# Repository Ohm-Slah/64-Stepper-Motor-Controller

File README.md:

# 64-Stepper-Motor-Controller
Controls an 8x8 array of stepper motors and RGB LED light strips, intended for audio/visual performance of a MIDI-like structure. You can certainly make this project with an FPGA, but I don't have much knowledge of FPGA's, so this project is written in C/C++ with the Arduino library included. Due to the incredible number of I/O, three Teensy microcontrollers are currently implemented, two Teensy 4.0's for I/O drivers (32 motors each), and one Teensy 4.1 for the 'main brain'. 

# Concetual initial design
General layout thoughts for such a large number of stepper motors and how to control them. Revision A is mostly based off of Concept #3.

# Revision A
This design is an attempt to create a fairly modular assembly for 64 stepper motor control. Each A4988 stepper driver can be extracted or replaced if neccessary. Eight total A4988 stepper drivers can be placed onto a single driver 'card'. These are designed to be edge-card connected to a larger board, the 32-stepper board. This board holds four driver cards, totalling to 32 stepper motors. There are 2 of these boards to total 64 motor drivers, with each having 20 74HC595 shift registers for I/O management, and visual indicator LED's for all outputs of the shift registers. Power is supplied to this board via a high-current connector. Both of these 32-stepper boards are then connected to a 'main board' containing the 3 microcontrollers, LED strip connections, and USB connection. 

## 8 Stepper PCB Card

## 32 Stepper PCB Board

## 64 Stepper PCB Board

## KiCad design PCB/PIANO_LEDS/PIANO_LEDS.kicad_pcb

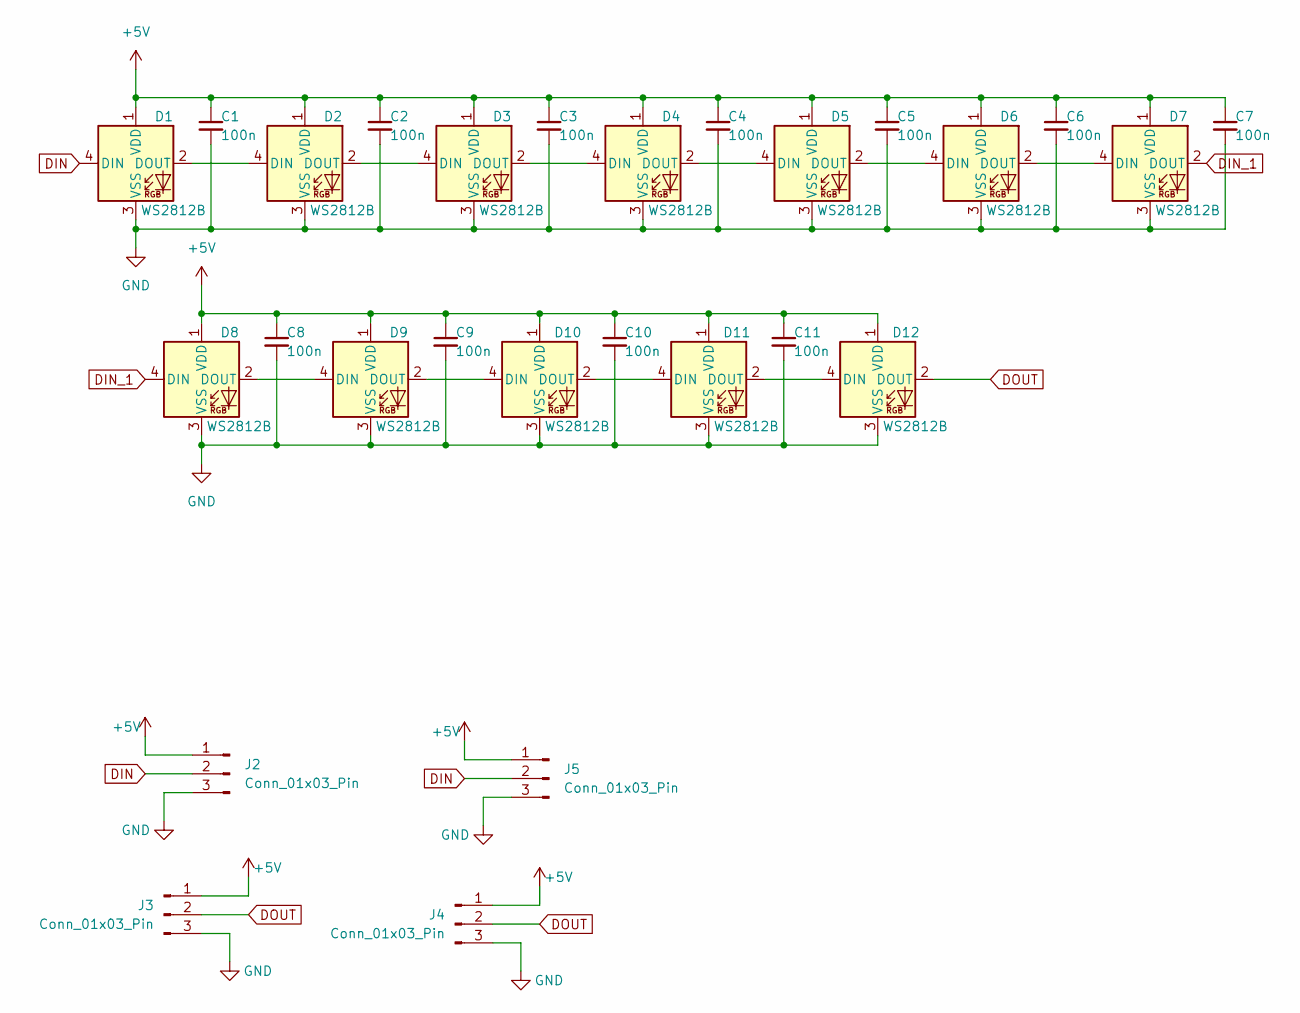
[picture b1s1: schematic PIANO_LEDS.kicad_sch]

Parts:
C1, C2, C3, C4, C5, C6, C7, C8, C9, C10, C11: 100n; C_0603_1608Metric
D1, D2, D3, D4, D5, D6, D7, D8, D9, D10, D11, D12: WS2812B; LED_WS2812B_PLCC4_5.0x5.0mm_P3.2mm
J2, J3, J4, J5: Conn_01x03_Pin; 3-PIN_SOLDER_EDGE

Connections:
+5V: C1.1, C2.1, C3.1, C4.1, C5.1, C6.1, C7.1, C8.1, C9.1, C10.1, C11.1, D1.1 (VDD), D2.1 (VDD), D3.1 (VDD), D4.1 (VDD), D5.1 (VDD), D6.1 (VDD), D7.1 (VDD), D8.1 (VDD), D9.1 (VDD), D10.1 (VDD), D11.1 (VDD), D12.1 (VDD), J2.1, J3.1, J4.1, J5.1
DIN: D1.4 (DIN), J2.2, J5.2
DIN_1: D7.2 (DOUT), D8.4 (DIN)
DOUT: D12.2 (DOUT), J3.2, J4.2
GND: C1.2, C2.2, C3.2, C4.2, C5.2, C6.2, C7.2, C8.2, C9.2, C10.2, C11.2, D1.3 (VSS), D2.3 (VSS), D3.3 (VSS), D4.3 (VSS), D5.3 (VSS), D6.3 (VSS), D7.3 (VSS), D8.3 (VSS), D9.3 (VSS), D10.3 (VSS), D11.3 (VSS), D12.3 (VSS), J2.3, J3.3, J4.3, J5.3
unnamed: D1.2 (DOUT), D2.4 (DIN)
unnamed: D2.2 (DOUT), D3.4 (DIN)
unnamed: D3.2 (DOUT), D4.4 (DIN)
unnamed: D4.2 (DOUT), D5.4 (DIN)
unnamed: D5.2 (DOUT), D6.4 (DIN)
unnamed: D6.2 (DOUT), D7.4 (DIN)
unnamed: D8.2 (DOUT), D9.4 (DIN)
unnamed: D9.2 (DOUT), D10.4 (DIN)
unnamed: D10.2 (DOUT), D11.4 (DIN)
unnamed: D11.2 (DOUT), D12.4 (DIN)

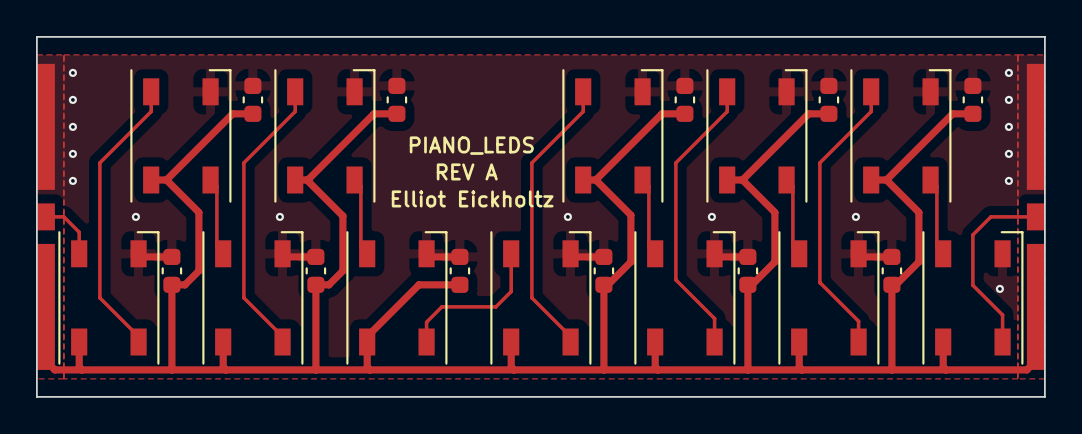
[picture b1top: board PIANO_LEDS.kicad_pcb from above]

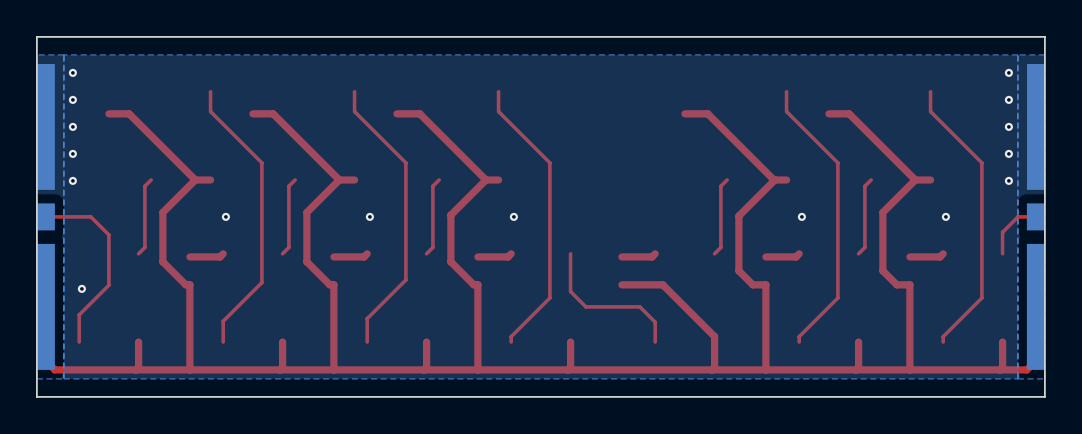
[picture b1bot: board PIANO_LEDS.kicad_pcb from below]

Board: 2 copper layers, 56.0 x 20.0 mm, 27 parts (2 on the bottom side), 15 nets.

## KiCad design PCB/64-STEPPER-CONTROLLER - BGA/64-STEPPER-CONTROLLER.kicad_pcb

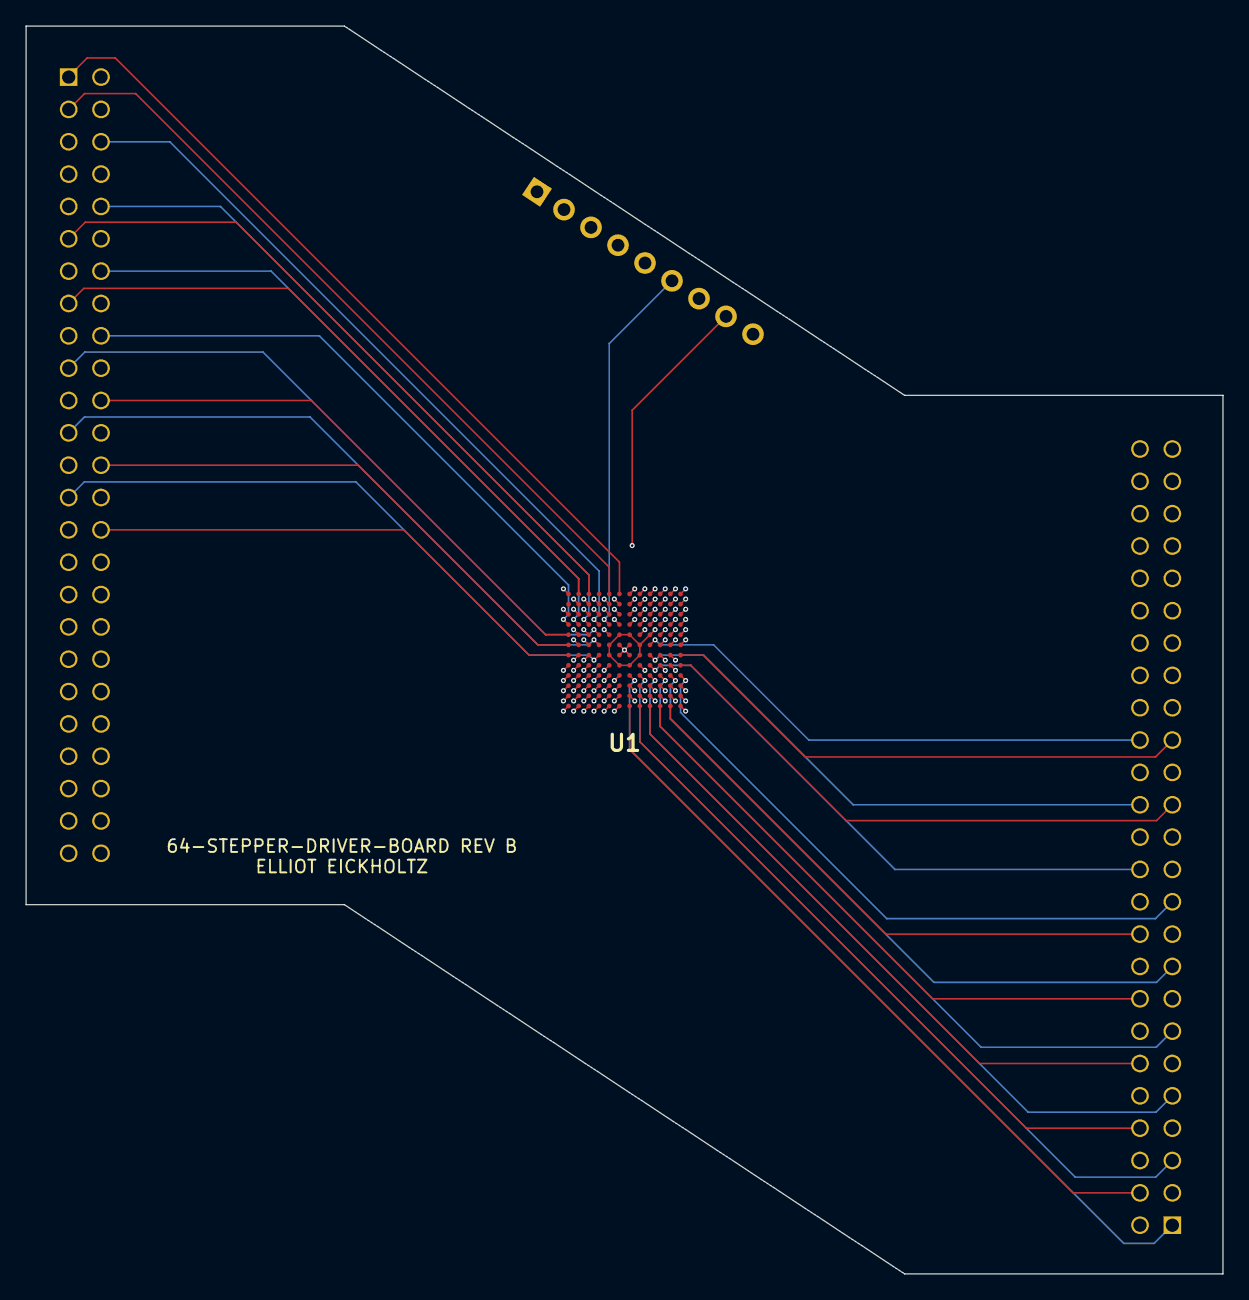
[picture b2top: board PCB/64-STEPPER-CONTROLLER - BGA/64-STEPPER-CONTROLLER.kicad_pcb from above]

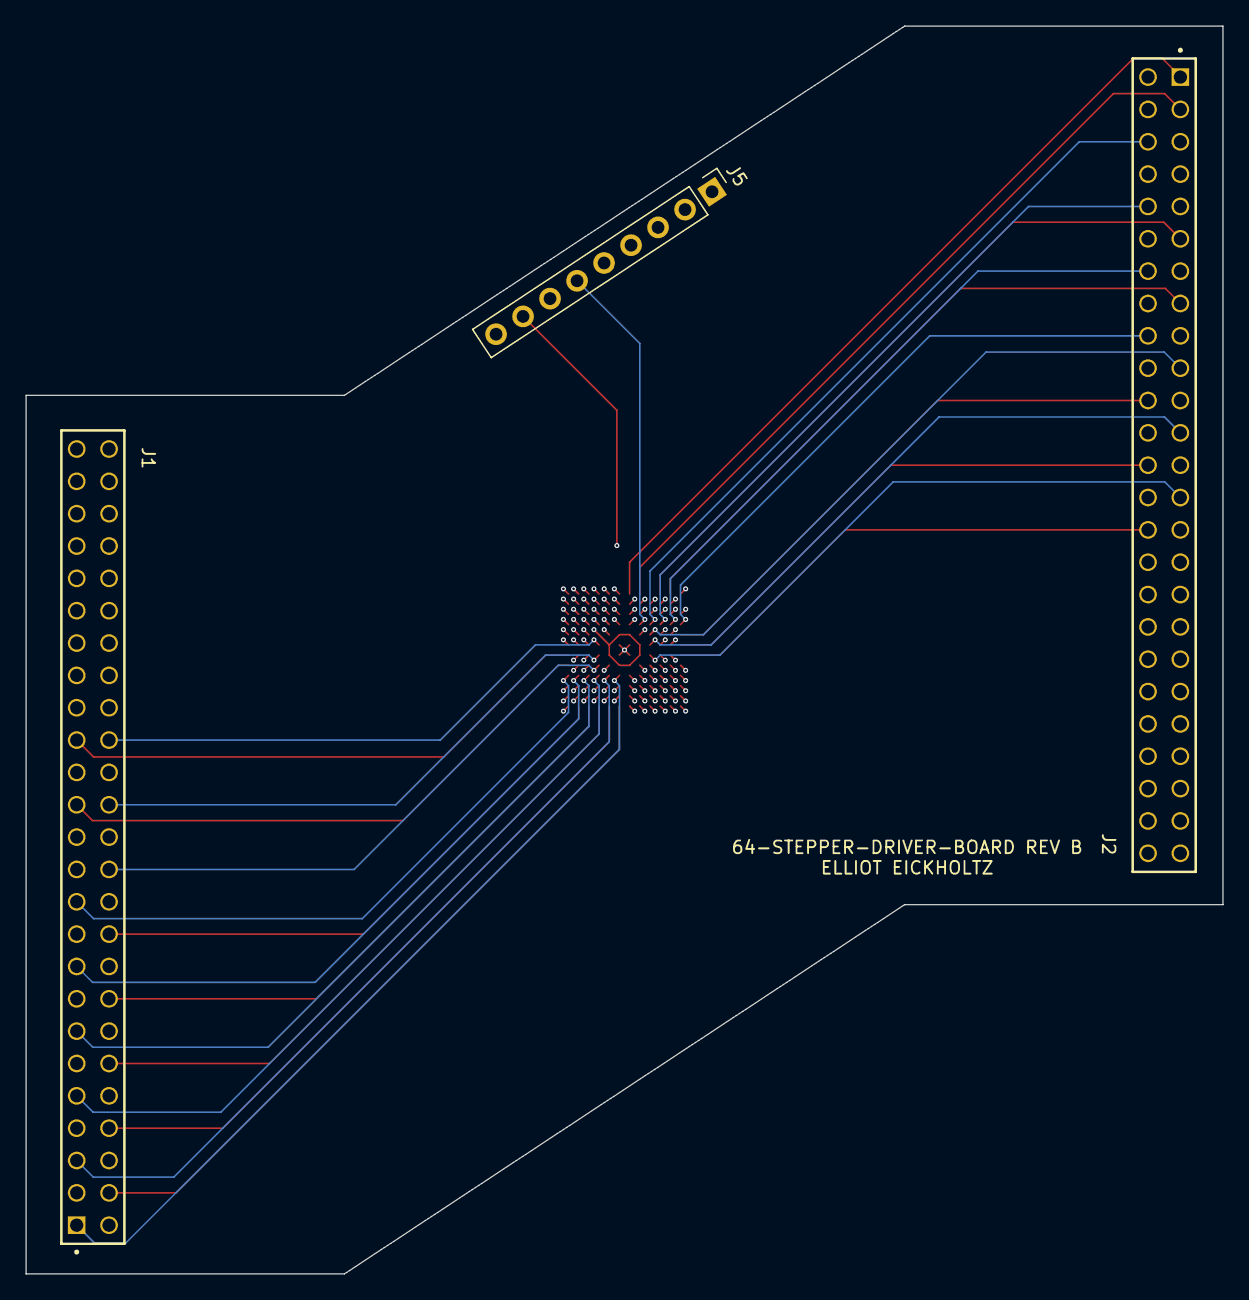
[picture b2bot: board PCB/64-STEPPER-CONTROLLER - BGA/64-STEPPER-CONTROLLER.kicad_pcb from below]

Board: 6 copper layers, 94.0 x 98.0 mm, 4 parts (3 on the bottom side), 69 nets.

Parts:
J1, J2: IPS1-125-01-S-D; SAMTEC_IPS1-125-01-S-D
J5: Conn_01x09; PinHeader_1x09_P2.54mm_Vertical
U1: STM32L471ZGJ6; BGA144C80P12X12_1000X1000X60

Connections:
1A1STEP: J1.08, U1.M8 (PE7)
1A2STEP: J1.06, U1.K8 (PE11)
1A3STEP: J1.04, U1.M7 (PF14)
1A4STEP: J1.02, U1.K7 (PG0)
1A5STEP: J1.07, U1.L8 (PE12)
1A6STEP: J1.05, U1.J8 (PE9)
1A7STEP: J1.03, U1.L7 (PE8)
1A8STEP: J1.01, U1.J7 (PG1)
2A1STEP: J1.16, U1.M10 (PE10)
2A2STEP: J1.14, U1.K10 (PB12)
2A3STEP: J1.12, U1.M9 (PF15)
2A4STEP: J1.10, U1.K9 (PB11)
2A5STEP: J1.15, U1.L10 (PE14)
2A6STEP: J1.13, U1.J10 (PB14)
2A7STEP: J1.11, U1.L9 (PE13)
2A8STEP: J1.09, U1.J9 (PB13)
3A1STEP: J1.24, U1.H9 (PD12)
3A2STEP: J1.22, U1.K12 (PD9)
3A3STEP: J1.20, U1.M11 (PE15)
3A4STEP: J1.18, U1.K11 (PD8)
3A5STEP: J1.23, U1.L12 (PB15)
3A6STEP: J1.21, U1.J12 (PD15)
3A7STEP: J1.19, U1.L11 (PB10)
3A8STEP: J1.17, U1.J11 (PD10)
4A1STEP: J1.32, U1.F9 (PG7)
4A2STEP: J1.30, U1.G11 (PG3)
4A3STEP: J1.28, U1.G9 (PG4)
4A4STEP: J1.26, U1.H11 (PD14)
4A5STEP: J1.31, U1.G12 (PG5)
4A6STEP: J1.29, U1.G10 (PD13)
4A7STEP: J1.27, U1.H12 (PG2)
4A8STEP: J1.25, U1.H10 (PD11)
5A1STEP: J2.08, U1.B5 (PB6)
5A2STEP: J2.06, U1.D4 (PC13)
5A3STEP: J2.04, U1.B6 (PG15)
5A4STEP: J2.02, U1.D6 (PG13)
5A5STEP: J2.07, U1.B4 (PE1)
5A6STEP: J2.05, U1.C4 (PB9)
5A7STEP: J2.03, U1.A5 (PB7)
5A8STEP: J2.01, U1.A6 (PG14)
6A1STEP: J2.16, U1.B2 (PE4)
6A2STEP: J2.14, U1.D2 (PC14-_OSC32_IN)
6A3STEP: J2.12, U1.B3 (PE3)
6A4STEP: J2.10, U1.D3 (PE6)
6A5STEP: J2.15, U1.A2 (PE0)
6A6STEP: J2.13, U1.C2 (PE5)
6A7STEP: J2.11, U1.A3 (PB8)
6A8STEP: J2.09, U1.C3 (PE2)
7A1STEP: J2.24, U1.F3 (PF5)
7A2STEP: J2.22, U1.E1 (PF6)
7A3STEP: J2.20, U1.E3 (PF0)
7A4STEP: J2.18, U1.D1 (PF4)
7A5STEP: J2.23, U1.F4 (PF3)
7A6STEP: J2.21, U1.E2 (PF1)
7A7STEP: J2.19, U1.E4 (PF2)
7A8STEP: J2.17, U1.C1 (PC15-_OSC32_OUT)
8A1STEP: J2.32, U1.H2 (PC0)
8A2STEP: J2.30, U1.G1 (PH1-_OSC_OUT)
8A3STEP: J2.28, U1.G3 (PF10)
8A4STEP: J2.26, U1.F1 (PF8)
8A5STEP: J2.31, U1.H3 (PC1)
8A6STEP: J2.29, U1.G2 (PH0-OSC_IN)
8A7STEP: J2.27, U1.G4 (PF9)
8A8STEP: J2.25, U1.F2 (PF7)
+5V: J5.9, U1.E6 (VDDIO2), U1.E7 (VDD), U1.E9 (VDD), U1.F5 (VDD), U1.F8 (VDDIO2), U1.G5 (VDD), U1.G8 (VDD), U1.H6 (VDD), U1.H7 (VDD), U1.K2 (VDDA)
GND: J1.47, J1.48, J1.49, J1.50, J2.47, J2.48, J2.49, J2.50, J5.5, U1.A1 (VSS), U1.E5 (VSS), U1.E8 (VSS), U1.F6 (VSS), U1.F7 (VSS), U1.G6 (VSS), U1.G7 (VSS), U1.H5 (VSS), U1.H8 (VSS), U1.J1 (VSSA), U1.M1 (VSS), U1.M12 (VSS)
MISO: J5.6, U1.D5 (PB4)
MOSI: J5.8, U1.C5 (PB5)
SCK: J5.7, U1.C6 (PB3)

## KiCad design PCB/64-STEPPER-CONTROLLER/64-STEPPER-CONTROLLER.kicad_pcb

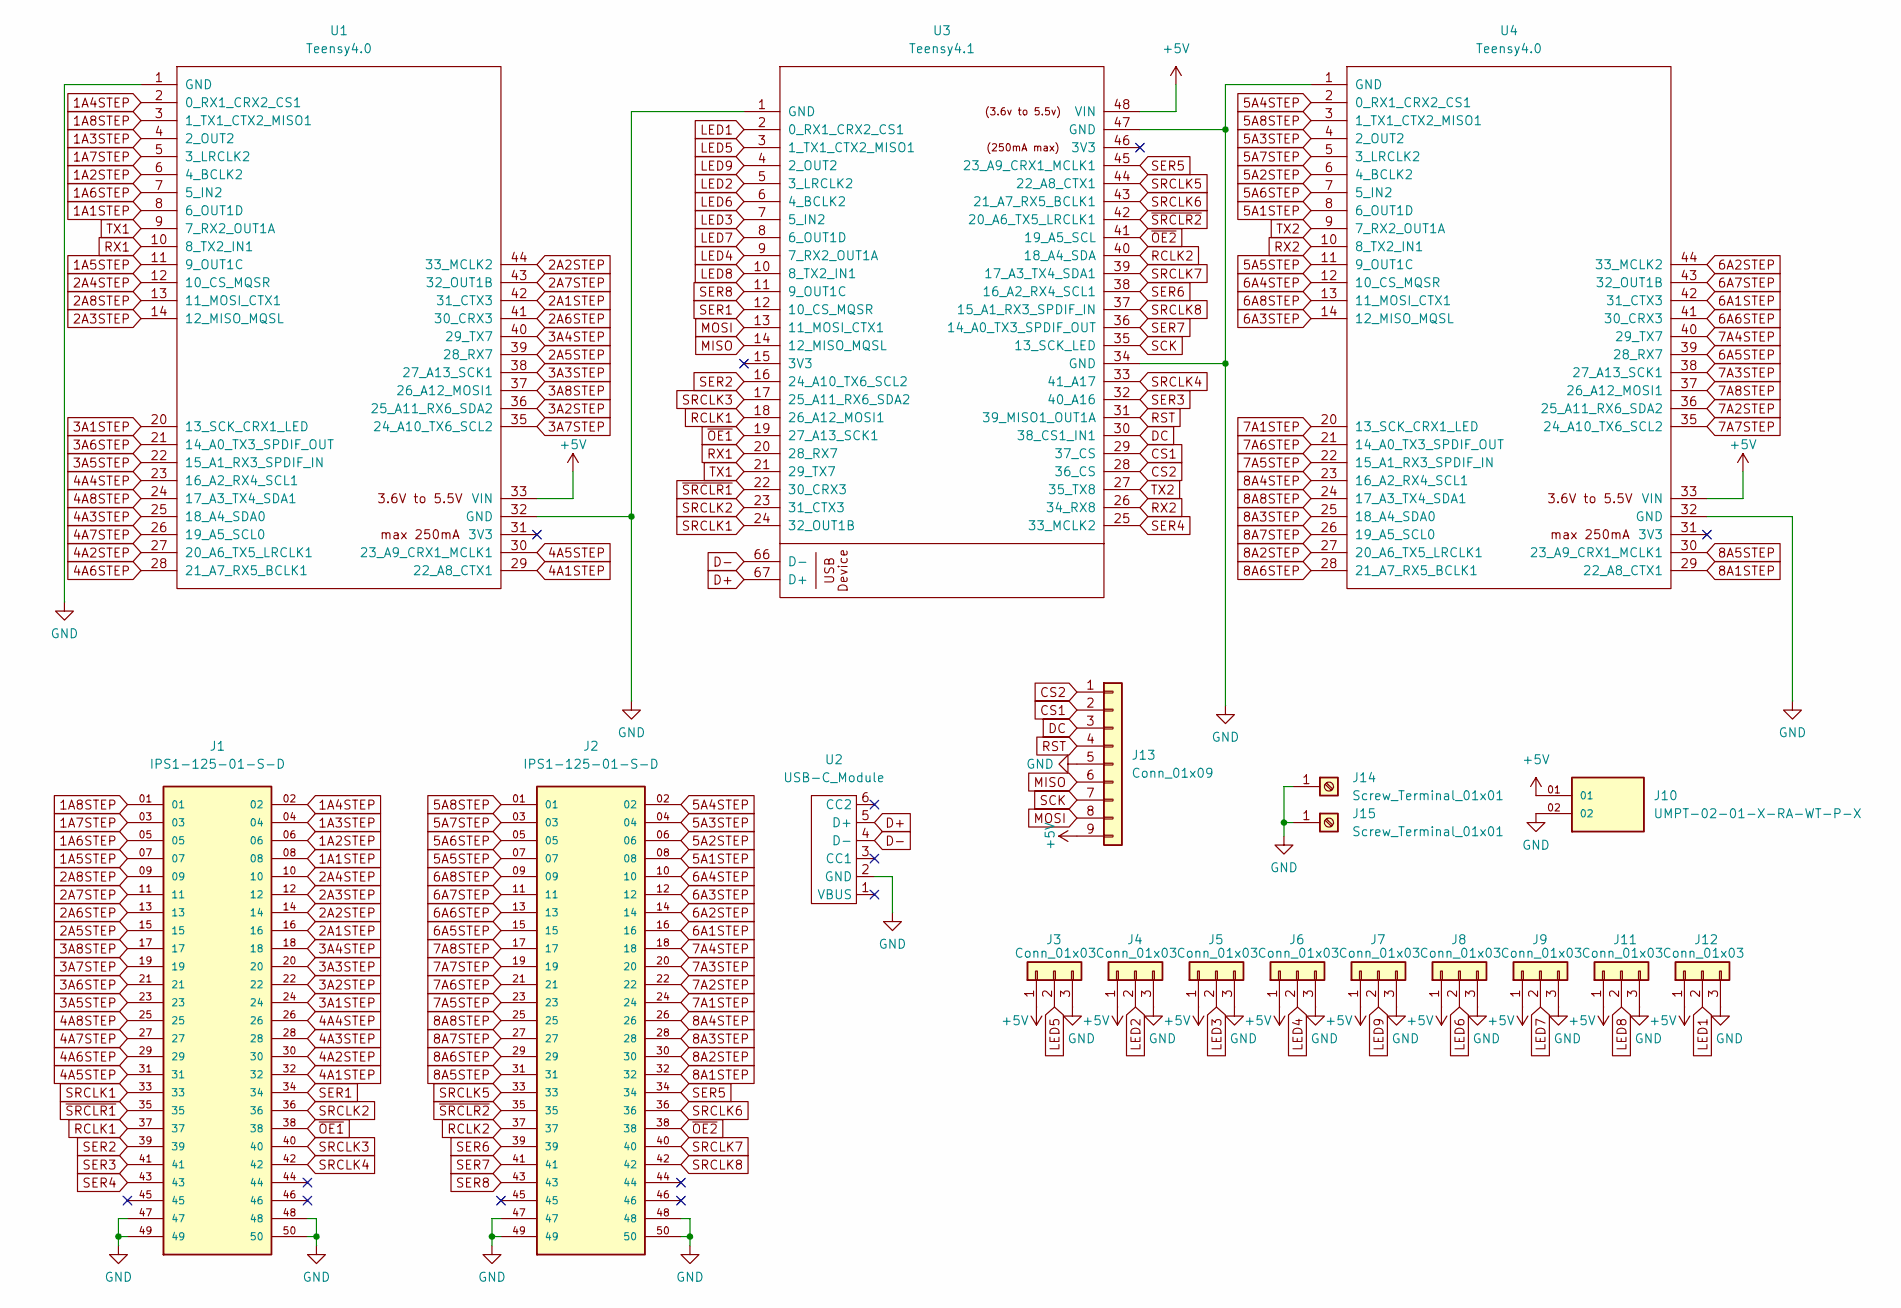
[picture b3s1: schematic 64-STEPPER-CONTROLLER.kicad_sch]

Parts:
J1, J2: IPS1-125-01-S-D; SAMTEC_IPS1-125-01-S-D; PARTREV R
J3, J4, J5, J6, J7, J8, J9, J11, J12: Conn_01x03; 3-PIN TERMINAL
J10: UMPT-02-01-X-RA-WT-P-X; SAMTEC_UMPT-02-01-X-RA-WT-P-X; PARTREV 4
J13: Conn_01x09; PinHeader_1x09_P2.54mm_Vertical
J14, J15: Screw_Terminal_01x01; MountingHole_2.2mm_M2_Pad
U1, U4: Teensy4.0; Teensy40
U2: USB-C_Module; USB-C-MODULE
U3: Teensy4.1; Teensy41

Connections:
1A1STEP: J1.08, U1.8 (6_OUT1D)
1A2STEP: J1.06, U1.6 (4_BCLK2)
1A3STEP: J1.04, U1.4 (2_OUT2)
1A4STEP: J1.02, U1.2 (0_RX1_CRX2_CS1)
1A5STEP: J1.07, U1.11 (9_OUT1C)
1A6STEP: J1.05, U1.7 (5_IN2)
1A7STEP: J1.03, U1.5 (3_LRCLK2)
1A8STEP: J1.01, U1.3 (1_TX1_CTX2_MISO1)
2A1STEP: J1.16, U1.42 (31_CTX3)
2A2STEP: J1.14, U1.44 (33_MCLK2)
2A3STEP: J1.12, U1.14 (12_MISO_MQSL)
2A4STEP: J1.10, U1.12 (10_CS_MQSR)
2A5STEP: J1.15, U1.39 (28_RX7)
2A6STEP: J1.13, U1.41 (30_CRX3)
2A7STEP: J1.11, U1.43 (32_OUT1B)
2A8STEP: J1.09, U1.13 (11_MOSI_CTX1)
3A1STEP: J1.24, U1.20 (13_SCK_CRX1_LED)
3A2STEP: J1.22, U1.36 (25_A11_RX6_SDA2)
3A3STEP: J1.20, U1.38 (27_A13_SCK1)
3A4STEP: J1.18, U1.40 (29_TX7)
3A5STEP: J1.23, U1.22 (15_A1_RX3_SPDIF_IN)
3A6STEP: J1.21, U1.21 (14_A0_TX3_SPDIF_OUT)
3A7STEP: J1.19, U1.35 (24_A10_TX6_SCL2)
3A8STEP: J1.17, U1.37 (26_A12_MOSI1)
4A1STEP: J1.32, U1.29 (22_A8_CTX1)
4A2STEP: J1.30, U1.27 (20_A6_TX5_LRCLK1)
4A3STEP: J1.28, U1.25 (18_A4_SDA0)
4A4STEP: J1.26, U1.23 (16_A2_RX4_SCL1)
4A5STEP: J1.31, U1.30 (23_A9_CRX1_MCLK1)
4A6STEP: J1.29, U1.28 (21_A7_RX5_BCLK1)
4A7STEP: J1.27, U1.26 (19_A5_SCL0)
4A8STEP: J1.25, U1.24 (17_A3_TX4_SDA1)
5A1STEP: J2.08, U4.8 (6_OUT1D)
5A2STEP: J2.06, U4.6 (4_BCLK2)
5A3STEP: J2.04, U4.4 (2_OUT2)
5A4STEP: J2.02, U4.2 (0_RX1_CRX2_CS1)
5A5STEP: J2.07, U4.11 (9_OUT1C)
5A6STEP: J2.05, U4.7 (5_IN2)
5A7STEP: J2.03, U4.5 (3_LRCLK2)
5A8STEP: J2.01, U4.3 (1_TX1_CTX2_MISO1)
6A1STEP: J2.16, U4.42 (31_CTX3)
6A2STEP: J2.14, U4.44 (33_MCLK2)
6A3STEP: J2.12, U4.14 (12_MISO_MQSL)
6A4STEP: J2.10, U4.12 (10_CS_MQSR)
6A5STEP: J2.15, U4.39 (28_RX7)
6A6STEP: J2.13, U4.41 (30_CRX3)
6A7STEP: J2.11, U4.43 (32_OUT1B)
6A8STEP: J2.09, U4.13 (11_MOSI_CTX1)
7A1STEP: J2.24, U4.20 (13_SCK_CRX1_LED)
7A2STEP: J2.22, U4.36 (25_A11_RX6_SDA2)
7A3STEP: J2.20, U4.38 (27_A13_SCK1)
7A4STEP: J2.18, U4.40 (29_TX7)
7A5STEP: J2.23, U4.22 (15_A1_RX3_SPDIF_IN)
7A6STEP: J2.21, U4.21 (14_A0_TX3_SPDIF_OUT)
7A7STEP: J2.19, U4.35 (24_A10_TX6_SCL2)
7A8STEP: J2.17, U4.37 (26_A12_MOSI1)
8A1STEP: J2.32, U4.29 (22_A8_CTX1)
8A2STEP: J2.30, U4.27 (20_A6_TX5_LRCLK1)
8A3STEP: J2.28, U4.25 (18_A4_SDA0)
8A4STEP: J2.26, U4.23 (16_A2_RX4_SCL1)
8A5STEP: J2.31, U4.30 (23_A9_CRX1_MCLK1)
8A6STEP: J2.29, U4.28 (21_A7_RX5_BCLK1)
8A7STEP: J2.27, U4.26 (19_A5_SCL0)
8A8STEP: J2.25, U4.24 (17_A3_TX4_SDA1)
+5V: J3.1, J4.1, J5.1, J6.1, J7.1, J8.1, J9.1, J10.01, J11.1, J12.1, J13.9, U1.33 (VIN), U3.48 (VIN), U4.33 (VIN)
CS1: J13.2, U3.29 (37_CS)
CS2: J13.1, U3.28 (36_CS)
D+: U2.5 (D+), U3.67 (D+)
D-: U2.4 (D-), U3.66 (D-)
DC: J13.3, U3.30 (38_CS1_IN1)
GND: J1.47, J1.48, J1.49, J1.50, J2.47, J2.48, J2.49, J2.50, J3.3, J4.3, J5.3, J6.3, J7.3, J8.3, J9.3, J10.02, J11.3, J12.3, J13.5, J14.1, J15.1, U1.1 (GND), U1.32 (GND), U2.2 (GND), U3.1 (GND), U3.34 (GND), U3.47 (GND), U4.1 (GND), U4.32 (GND)
LED1: J12.2, U3.2 (0_RX1_CRX2_CS1)
LED2: J4.2, U3.5 (3_LRCLK2)
LED3: J5.2, U3.7 (5_IN2)
LED4: J6.2, U3.9 (7_RX2_OUT1A)
LED5: J3.2, U3.3 (1_TX1_CTX2_MISO1)
LED6: J8.2, U3.6 (4_BCLK2)
LED7: J9.2, U3.8 (6_OUT1D)
LED8: J11.2, U3.10 (8_TX2_IN1)
LED9: J7.2, U3.4 (2_OUT2)
MISO: J13.6, U3.14 (12_MISO_MQSL)
MOSI: J13.8, U3.13 (11_MOSI_CTX1)
RCLK1: J1.37, U3.18 (26_A12_MOSI1)
RCLK2: J2.37, U3.40 (18_A4_SDA)
RST: J13.4, U3.31 (39_MISO1_OUT1A)
RX1: U1.10 (8_TX2_IN1), U3.20 (28_RX7)
RX2: U3.26 (34_RX8), U4.10 (8_TX2_IN1)
SCK: J13.7, U3.35 (13_SCK_LED)
SER1: J1.34, U3.12 (10_CS_MQSR)
SER2: J1.39, U3.16 (24_A10_TX6_SCL2)
SER3: J1.41, U3.32 (40_A16)
SER4: J1.43, U3.25 (33_MCLK2)
SER5: J2.34, U3.45 (23_A9_CRX1_MCLK1)
SER6: J2.39, U3.38 (16_A2_RX4_SCL1)
SER7: J2.41, U3.36 (14_A0_TX3_SPDIF_OUT)
SER8: J2.43, U3.11 (9_OUT1C)
SRCLK1: J1.33, U3.24 (32_OUT1B)
SRCLK2: J1.36, U3.23 (31_CTX3)
SRCLK3: J1.40, U3.17 (25_A11_RX6_SDA2)
SRCLK4: J1.42, U3.33 (41_A17)
SRCLK5: J2.33, U3.44 (22_A8_CTX1)
SRCLK6: J2.36, U3.43 (21_A7_RX5_BCLK1)
SRCLK7: J2.40, U3.39 (17_A3_TX4_SDA1)
SRCLK8: J2.42, U3.37 (15_A1_RX3_SPDIF_IN)
TX1: U1.9 (7_RX2_OUT1A), U3.21 (29_TX7)
TX2: U3.27 (35_TX8), U4.9 (7_RX2_OUT1A)
~OE1: J1.38, U3.19 (27_A13_SCK1)
~OE2: J2.38, U3.41 (19_A5_SCL)
~SRCLR1: J1.35, U3.22 (30_CRX3)
~SRCLR2: J2.35, U3.42 (20_A6_TX5_LRCLK1)

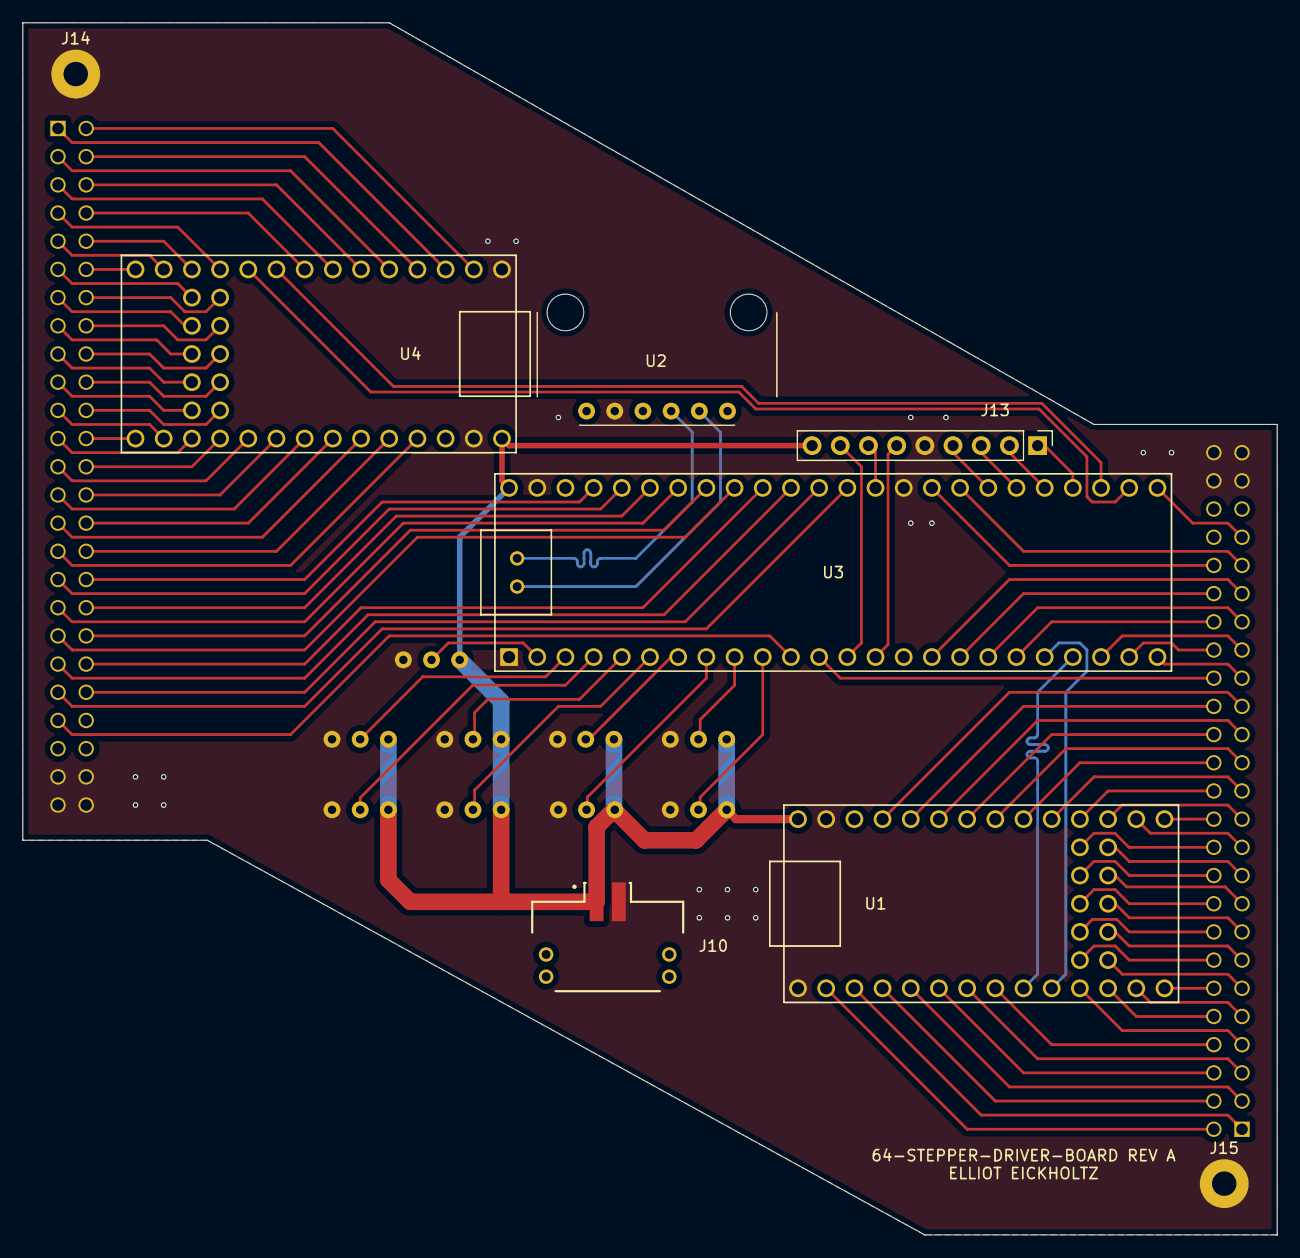
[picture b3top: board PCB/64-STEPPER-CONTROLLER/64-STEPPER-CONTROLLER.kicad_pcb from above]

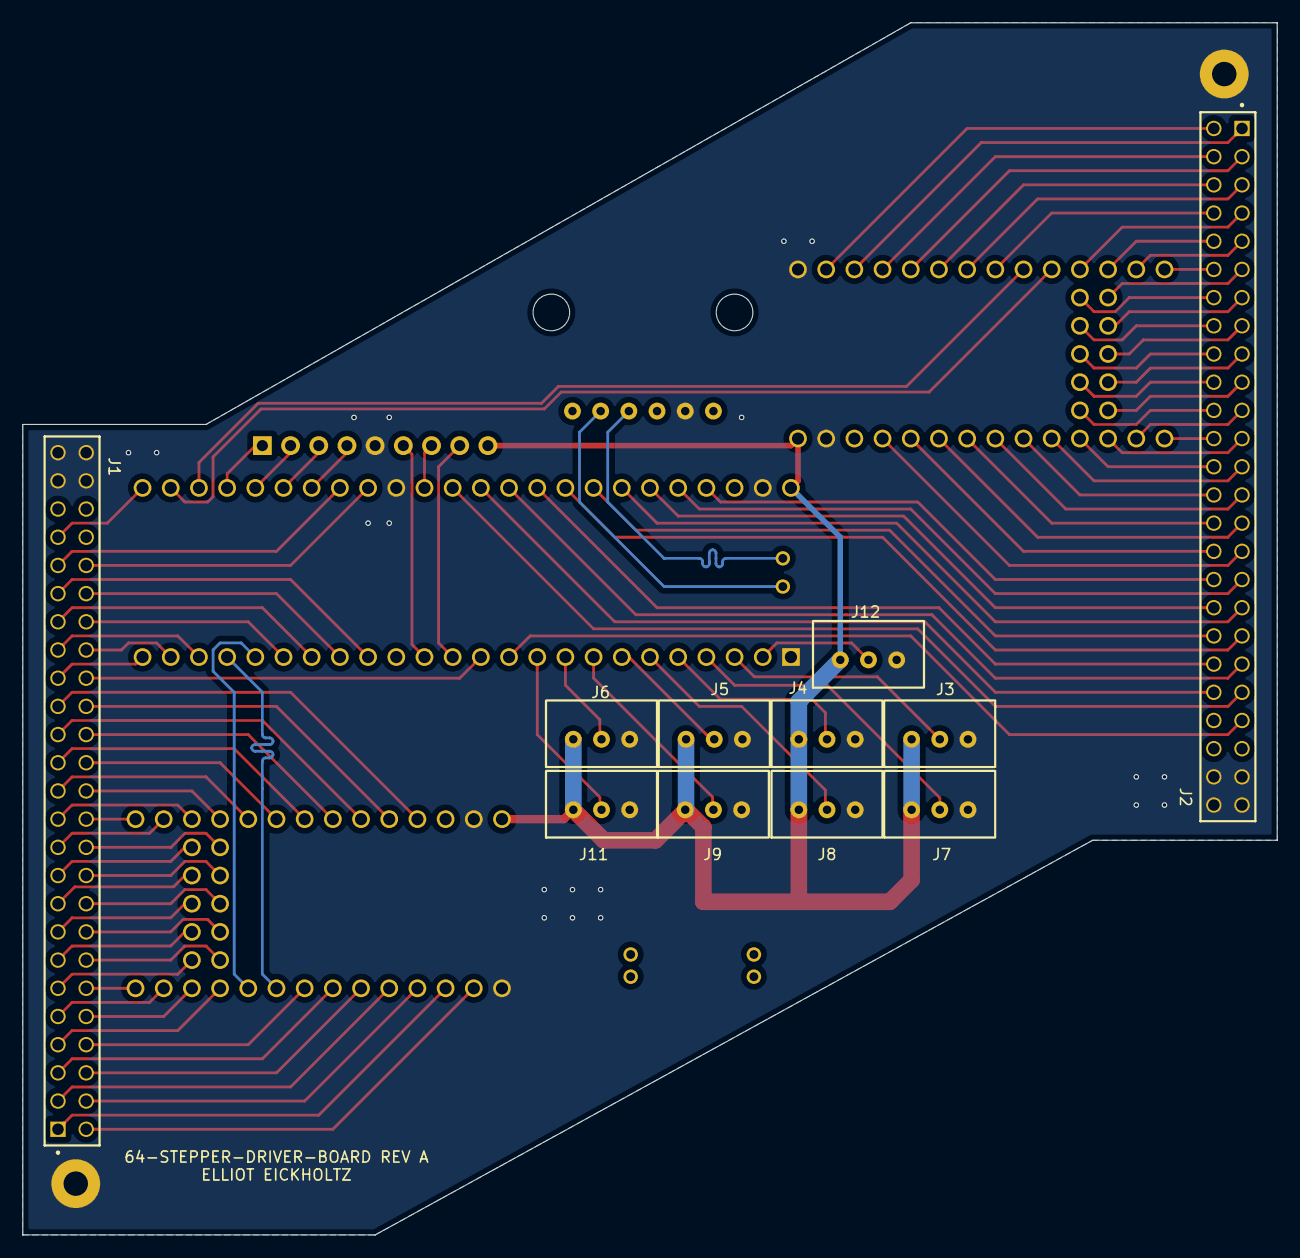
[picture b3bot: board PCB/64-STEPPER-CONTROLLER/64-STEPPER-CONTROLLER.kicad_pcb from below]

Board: 2 copper layers, 113.0 x 109.2 mm, 19 parts (11 on the bottom side), 110 nets.

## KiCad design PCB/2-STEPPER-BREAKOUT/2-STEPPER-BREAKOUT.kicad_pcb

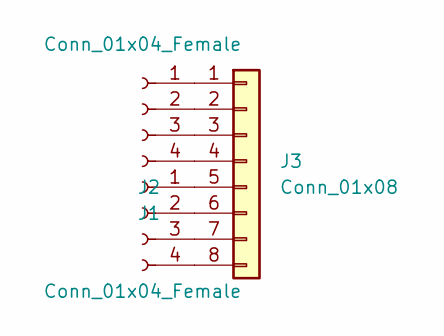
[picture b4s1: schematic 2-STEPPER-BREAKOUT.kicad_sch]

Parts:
J1, J2: Conn_01x04_Female; PinSocket_1x04_P2.54mm_Horizontal
J3: Conn_01x08; PinHeader_2x04_P2.54mm_edge

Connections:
unnamed: J1.1, J3.1
unnamed: J1.2, J3.2
unnamed: J1.3, J3.3
unnamed: J1.4, J3.4
unnamed: J2.1, J3.5
unnamed: J2.2, J3.6
unnamed: J2.3, J3.7
unnamed: J2.4, J3.8

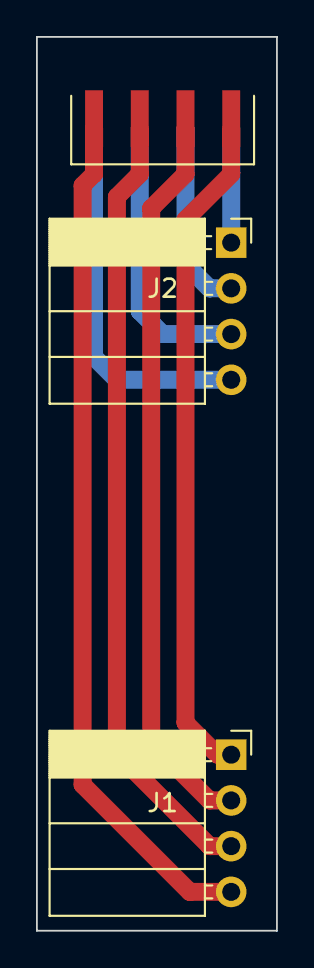
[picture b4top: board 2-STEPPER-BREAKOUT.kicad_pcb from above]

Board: 2 copper layers, 13.3 x 49.7 mm, 3 parts (0 on the bottom side), 8 nets.

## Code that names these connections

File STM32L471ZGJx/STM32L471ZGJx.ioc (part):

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Mcu.Name=STM32L471Z(E-G)Jx
Mcu.Package=UFBGA144
Mcu.UserName=STM32L471ZGJx
PB10.Signal=GPIO_Output
PB11.Signal=GPIO_Output
PB12.Signal=GPIO_Output
PB13.Signal=GPIO_Output
PB14.Signal=GPIO_Output
PB15.Signal=GPIO_Output
PB3\ (JTDO-TRACESWO).Mode=Full_Duplex_Master
PB3\ (JTDO-TRACESWO).Signal=SPI1_SCK
PB4\ (NJTRST).Mode=Full_Duplex_Master
PB4\ (NJTRST).Signal=SPI1_MISO
PB5.Mode=Full_Duplex_Master
PB5.Signal=SPI1_MOSI
PB6.Signal=GPIO_Output
PB7.Signal=GPIO_Output
PB8.Signal=GPIO_Output
PB9.Signal=GPIO_Output
PC0.Signal=GPIO_Output
PC1.Signal=GPIO_Output
PC13.Signal=GPXTI13
PC14-OSC32_IN\ (PC14).Signal=GPIO_Output
PC15-OSC32_OUT\ (PC15).Signal=GPIO_Output
PD10.Signal=GPIO_Output
PD11.Signal=GPIO_Output
PD12.Signal=GPIO_Output
PD13.Signal=GPIO_Output
PD14.Signal=GPIO_Output
PD15.Signal=GPIO_Output
PD8.Signal=GPIO_Output
PD9.Signal=GPIO_Output
PE0.Signal=GPIO_Output
PE1.Signal=GPIO_Output
PE10.Signal=GPIO_Output
PE11.Signal=GPIO_Output
PE12.Signal=GPIO_Output
PE13.Signal=GPIO_Output
PE14.Signal=GPIO_Output
PE15.Signal=GPIO_Output
PE2.Signal=GPIO_Output
PE3.Signal=GPIO_Output
PE4.Signal=GPIO_Output
PE5.Signal=GPIO_Output
PE6.Signal=GPIO_Output
PE7.Signal=GPIO_Output
PE8.Signal=GPIO_Output
PE9.Signal=GPIO_Output
PF0.Signal=GPIO_Output
PF1.Signal=GPIO_Output
PF10.Signal=GPIO_Output
PF14.Signal=GPIO_Output
PF15.Signal=GPIO_Output
PF2.Signal=GPIO_Output
PF3.Signal=GPIO_Output
PF4.Signal=GPIO_Output
PF5.Signal=GPIO_Output
PF6.Signal=GPIO_Output
PF7.Signal=GPIO_Output
PF8.Signal=GPIO_Output
PF9.Signal=GPIO_Output
PG0.Signal=GPIO_Output
PG1.Signal=GPIO_Output
PG13.Signal=GPIO_Output
PG14.Signal=GPIO_Output
PG15.Signal=GPIO_Output
PG2.Signal=GPIO_Output
PG3.Signal=GPIO_Output
PG4.Signal=GPIO_Output
PG5.Signal=GPIO_Output
PG7.Signal=GPIO_Output
PH0-OSC_IN\ (PH0).Signal=GPIO_Output
PH1-OSC_OUT\ (PH1).Signal=GPIO_Output
RCC.HSE_VALUE=8000000
board=custom

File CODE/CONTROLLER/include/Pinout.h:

/*
 * File name: Pinout.h -> CONTROLLER
 * Project: 64 Motor Driver
 * Author: Elliot Eickholtz
 * Purpose: Define all pins used on the Teensy 4.1.
 * 
*/

#ifndef PINOUT_H
#define PINOUT_H

//  *Initialize all stepper driver freq pins to a unique identifier*  //
//  *--------------------------------------------------------------*  //

// Latch clock
#define RCLK1 26
#define RCLK2 18

// Data in
#define SER1 10
#define SER2 24
#define SER3 40
#define SER4 33

#define SER5 23
#define SER6 16
#define SER7 14
#define SER8 9

// Shift clock
#define SRCLK1 32
#define SRCLK2 31
#define SRCLK3 25
#define SRCLK4 41

#define SRCLK5 22
#define SRCLK6 21
#define SRCLK7 17
#define SRCLK8 15

// Reset
#define SRCLR1 30
#define SRCLR2 20

// Output enable
#define OE1 27
#define OE2 19

//  *^^^^^^^^^^^^^^^^^^^^^^^^^^^^^^^^^^^^^^^^^^^^^^^^^^^^^^^^^^^^^^*  //

//  *Define shift register pin order*   //
//  *-------------------------------*   //

#define DIR01 1
#define DIR05 2
#define A01EN 3
#define A05EN 4
#define A1MS1 5
#define A5MS1 6
#define A1MS2 7
#define A5MS2 8
#define A1MS3 9
#define A5MS3 10
#define DIR02 11
#define DIR06 12
#define A02EN 13
#define A06EN 14
#define A2MS1 15
#define A6MS1 16
#define A2MS2 17
#define A6MS2 18
#define A2MS3 19
#define A6MS3 20
#define DIR03 21
#define DIR07 22
#define A03EN 23
#define A07EN 24
#define A3MS1 25
#define A7MS1 26
#define A3MS2 27
#define A7MS2 28
#define A3MS3 29
#define A7MS3 30
#define DIR04 31
#define DIR08 32
#define A04EN 33
#define A08EN 34
#define A4MS1 35
#define A8MS1 36
#define A4MS2 37
#define A8MS2 38
#define A4MS3 39
#define A8MS3 40

uint8_t enablePins[8] = {A01EN, A02EN, A03EN, A04EN, A05EN, A06EN, A07EN, A08EN};
uint8_t directionPins[8] = {DIR01, DIR02, DIR03, DIR04, DIR05, DIR06, DIR07, DIR08};
uint8_t MS1Pins[8] = {A1MS1, A2MS1, A3MS1, A4MS1, A5MS1, A6MS1, A7MS1, A8MS1};
uint8_t MS2Pins[8] = {A1MS2, A2MS2, A3MS2, A4MS2, A5MS2, A6MS2, A7MS2, A8MS2};
uint8_t MS3Pins[8] = {A1MS3, A2MS3, A3MS3, A4MS3, A5MS3, A6MS3, A7MS3, A8MS3};

//  *^^^^^^^^^^^^^^^^^^^^^^^^^^^^^^^*   //

#endif  // PINOUT_H

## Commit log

2022-05-06 initial commit
    Contains initial conceptual dwg
2022-05-07 minimal change
2022-05-12 Concept #2 added
2022-05-12 SECOND CONCEPT ADDED TO
2022-05-12 ADDED REFERENCE PICS
2022-05-12 File and folder project setup
    Based off of 2nd conceptual design
2022-05-12 workspace adjustment
2022-05-14 initial schematic layout
2022-05-17 PCB Routing for Stepper Card
2022-05-18 ignore
2022-05-18 begin 32 stepper board
2022-05-18 final rev 1 design, no slots
2022-05-18 Name change, final addition before prototype order
2022-05-18 folder name change
2022-05-19 initial 32-driver layout
2022-05-19 MORE 32-STEPPER LAYOUT WORK
2022-05-20 progress
2022-05-23 added more connectors
2022-05-25 LED's and resistors placed
2022-05-27 re-routing bottom layer
2022-05-31 cleanup before DRC Errors
2022-06-01 messing around with plugins
2022-06-03 Final checks for 32-stepper driver
2022-06-06 generate gerber for price check
2022-06-09 final adjustments
2022-06-09 32- driver board gerber generation
2022-06-09 order placed
2022-06-10 64 motor initial setup
2022-06-12 overview
2022-06-13 basic pin definitions added
2022-06-14 begin testing
2022-06-14 basic code setup
2022-06-14 Serial interface setup
2022-06-14 able to upload
2022-06-15 Shift register general layout
2022-06-15 move file location
2022-06-16 readme updates, 3d model paths updated
2022-06-16 readme updates
2022-06-16 progress in code layout
2022-06-17 update gitignore
2022-06-17 Revert "update gitignore"
    This reverts commit 6e58a190580f49eac1285e80ab7aa617997ae66b.
2022-06-17 Revert "Delete PCB/32-STEPPER-DRIVER-BOARD/32-STEPPER-DRIVER-BOARD-backups directory"
    This reverts commit 177caab1064322d9d7df6012cbe4820df753b896.
2022-06-17 Revert "Delete PCB/64-STEPPER-CONTROLLER/64-STEPPER-CONTROLLER-backups directory"
    This reverts commit f72b966d8d27d6964fcca2892ab00198c4950c66.
2022-06-17 Revert "Delete PCB/8-STEPPER-DRIVER-CARD/8-STEPPER-DRIVER-CARD-backups directory"
    This reverts commit 18a410249bb65aef49d1b6562cd3212f99cfb8d6.
2022-06-17 Creating classes
2022-06-23 first successful motor spinning
2022-06-23 finished basic shift register control
2022-06-23 classes cleaned
2022-07-01 Serial setup
2022-07-01 processing gui testing added
2022-07-01 python gui testing added
2022-07-01 serial research and development
2022-07-08 serial specs work
2022-07-10 Finish design of main board
2022-07-11 final changes to 64-pcb and testing renders
2022-07-13 begin stepper wiring breakout board
2022-07-13 pic for readme
2022-07-14 Finish 2-motor breakout, submit order for 2 & 64
2022-07-15 Pinout and beginning controller code
2022-07-20 64-stepper driver debugging
2022-07-22 gui testing
2022-07-25 setup processing 3 and begin serial work
2022-07-26 conceptual layout update
2022-07-27 more work
2022-07-27 Attempting to set up a communication protocol
2022-08-01 serial driver progress
2022-08-08 midid tests
2022-08-17 communication protocol now working
2022-08-22 Added light controls and basic midi functions
2022-09-11 added lighting
2022-09-13 added matrix motor controls ground work
2022-10-13 fft tests
2022-11-22 BGA general setup
2022-11-29 small changes
2022-12-07 small changes lol
2022-12-13 midi tool development
2022-12-13 small chnages
2022-12-15 importing and visualizing data
2022-12-19 ramping applied
2022-12-19 Midi tool changes
2022-12-19 Clean up serial print statements
2022-12-19 Create BOM for 32-Board
2022-12-20 Readme Updated
2022-12-21 Changed communication protocol, basic usage added
2022-12-21 removed microstepping ramping
2022-12-21 Added segmented lighting for separate notes
2023-01-13 update documentation
2024-01-17 Remove STM32 stuff
2024-01-17 Change to 4 channel
    Testing success, time for the crunch.
2024-02-01 Add cable controls
    Not tested, but need to branch off of this for other ideas.
2024-02-03 Starting layout
2024-02-07 Design complete
